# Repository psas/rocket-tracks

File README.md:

rocket-tracks
=============

CAD files for the Rocket Tracks project

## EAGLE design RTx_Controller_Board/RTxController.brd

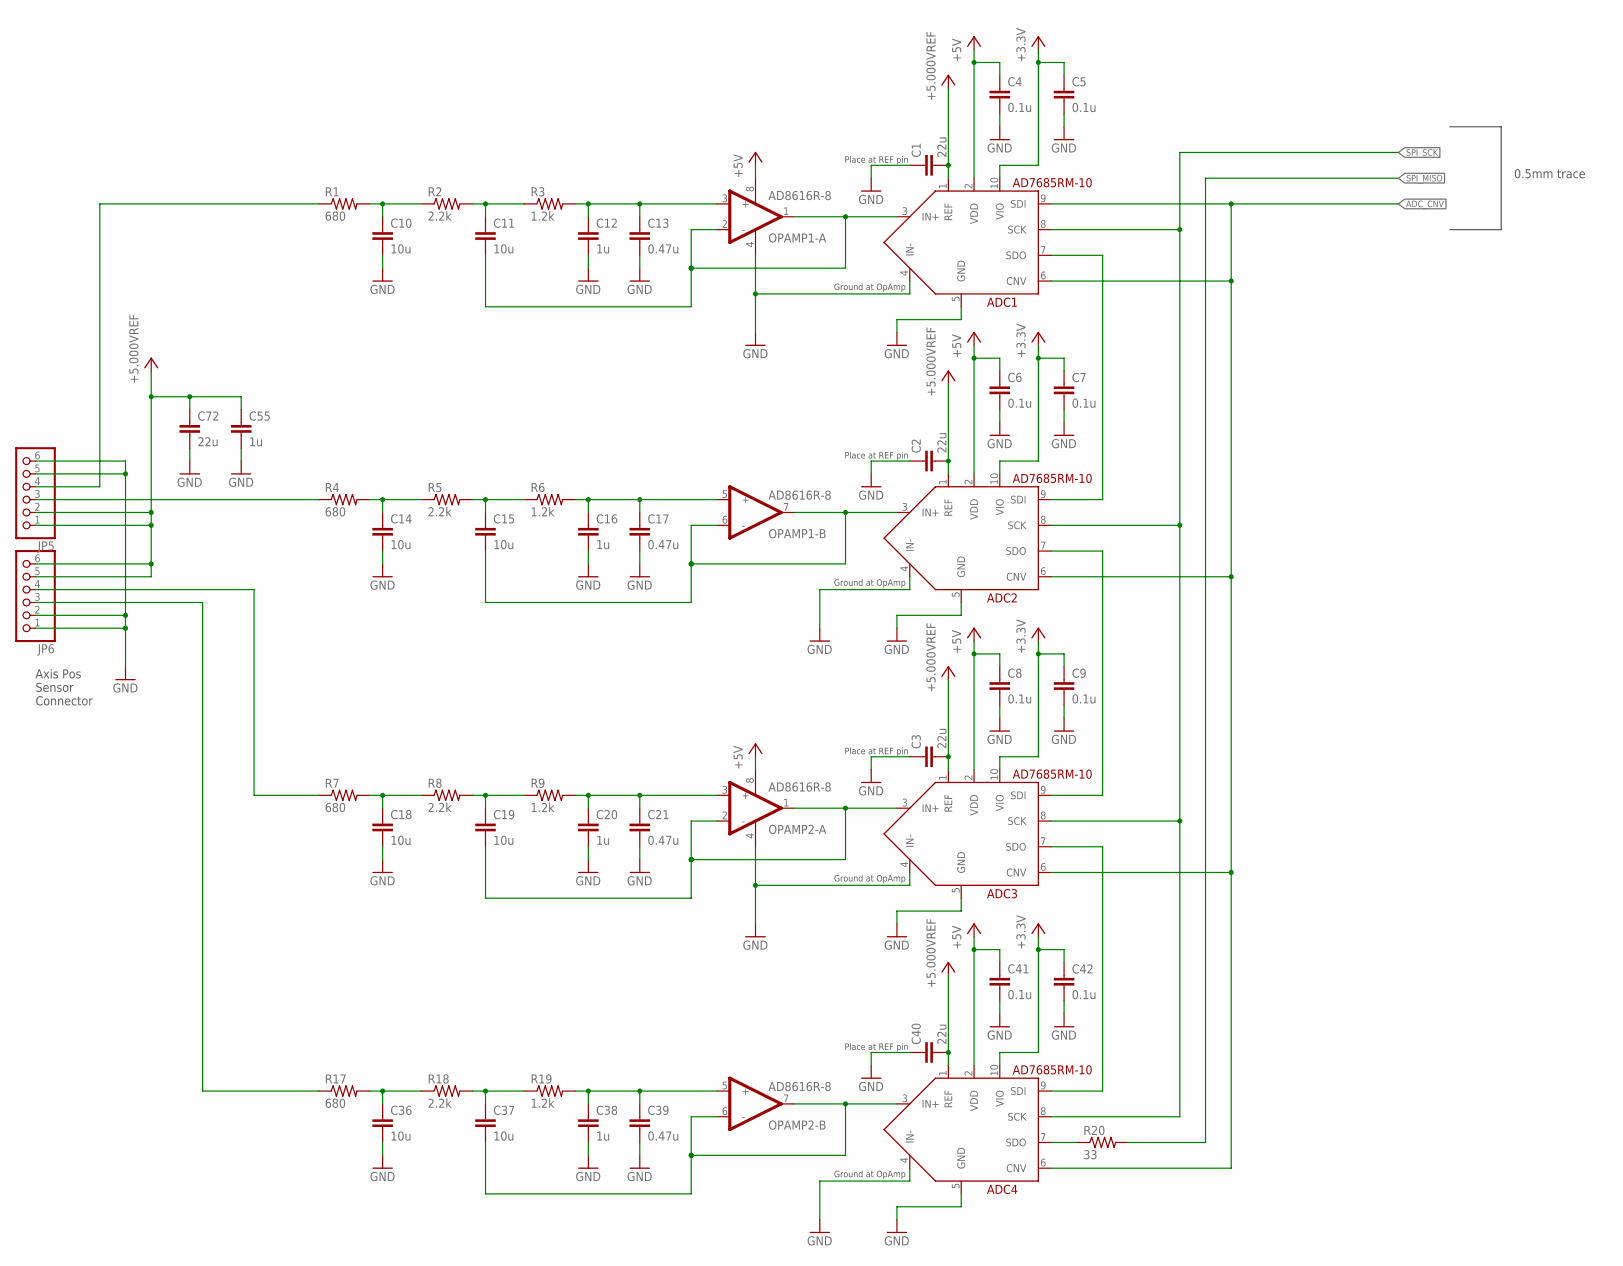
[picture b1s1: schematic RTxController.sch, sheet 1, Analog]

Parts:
ADC1, ADC2, ADC3, ADC4: AD7685RM-10; MSOP-10
C1, C2, C3, C40, C72: 22u; C1206
C4, C5, C6, C7, C8, C9, C41, C42: 0.1u; C0402
C10, C11, C14, C15, C18, C19, C36, C37: 10u; C1206
C12, C16, C20, C38, C55: 1u; C0805
C13, C17, C21, C39: 0.47u; C0805
JP5, JP6: PINHD-1X6; 1X06
OPAMP1, OPAMP2: AD8616R-8; SOIC8
R1, R4, R7, R17: 680; R0402
R2, R5, R8, R18: 2.2k; R0402
R3, R6, R9, R19: 1.2k; R0402
R20: 33; R0402

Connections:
+3.3V: ADC1.10 (VIO), ADC2.10 (VIO), ADC3.10 (VIO), ADC4.10 (VIO), C5.1, C7.1, C9.1, C42.1; also elsewhere on the board
+5.000VREF: ADC1.1 (REF), ADC2.1 (REF), ADC3.1 (REF), ADC4.1 (REF), C1.2, C2.2, C3.2, C40.2, C55.1, C72.1, JP5.1, JP5.2, JP6.5, JP6.6; also elsewhere on the board
+5V: ADC1.2 (VDD), ADC2.2 (VDD), ADC3.2 (VDD), ADC4.2 (VDD), C4.1, C6.1, C8.1, C41.1, OPAMP1.8 (V+), OPAMP2.8 (V+); also elsewhere on the board
ADC1_IN+: ADC1.3 (IN+), C11.2, OPAMP1.1 (OUT_A), OPAMP1.2 (-)
ADC2_IN+: ADC2.3 (IN+), C15.2, OPAMP1.6 (-), OPAMP1.7 (OUT_B)
ADC3_IN+: ADC3.3 (IN+), C19.2, OPAMP2.1 (OUT_A), OPAMP2.2 (-)
ADC4_IN: ADC4.3 (IN+), C37.2, OPAMP2.6 (-), OPAMP2.7 (OUT_B)
ADC_CNV: ADC1.6 (CNV), ADC1.9 (SDI), ADC2.6 (CNV), ADC3.6 (CNV), ADC4.6 (CNV); also elsewhere on the board
AXIS3_IN: JP6.4, R7.1
AXIS4_IN: JP6.3, R17.1
GND: ADC1.4 (IN-), ADC1.5 (GND), ADC2.4 (IN-), ADC2.5 (GND), ADC3.4 (IN-), ADC3.5 (GND), ADC4.4 (IN-), ADC4.5 (GND), C1.1, C2.1, C3.1, C4.2, C5.2, C6.2, C7.2, C8.2, C9.2, C10.2, C12.2, C13.2, C14.2, C16.2, C17.2, C18.2, C20.2, C21.2, C36.2, C38.2, C39.2, C40.1, C41.2, C42.2, C55.2, C72.2, JP5.5, JP5.6, JP6.1, JP6.2, OPAMP1.4 (V-), OPAMP2.4 (V-); also elsewhere on the board
LAT_AXIS_IN: JP5.4, R1.1
unnamed: C12.1, C13.1, OPAMP1.3 (+), R3.2
unnamed: C16.1, C17.1, OPAMP1.5 (+), R6.2
unnamed: C38.1, C39.1, OPAMP2.5 (+), R19.2
unnamed: C11.1, R2.2, R3.1
unnamed: C37.1, R18.2, R19.1
unnamed: C15.1, R5.2, R6.1
unnamed: C36.1, R17.2, R18.1
unnamed: C14.1, R4.2, R5.1
unnamed: C20.1, C21.1, OPAMP2.3 (+), R9.2
unnamed: C19.1, R8.2, R9.1
unnamed: C18.1, R7.2, R8.1
unnamed: C10.1, R1.2, R2.1
SDO1: ADC1.7 (SDO), ADC2.9 (SDI)
SDO2: ADC2.7 (SDO), ADC3.9 (SDI)
SDO3: ADC3.7 (SDO), ADC4.9 (SDI)
SDO4: ADC4.7 (SDO), R20.1
SPI_MISO: R20.2; also elsewhere on the board
SPI_SCK: ADC1.8 (SCK), ADC2.8 (SCK), ADC3.8 (SCK), ADC4.8 (SCK); also elsewhere on the board
VERT_AXIS_IN: JP5.3, R4.1

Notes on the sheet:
Axis Pos Sensor Connector
Ground at OpAmp
Place at REF pin
0.5mm trace

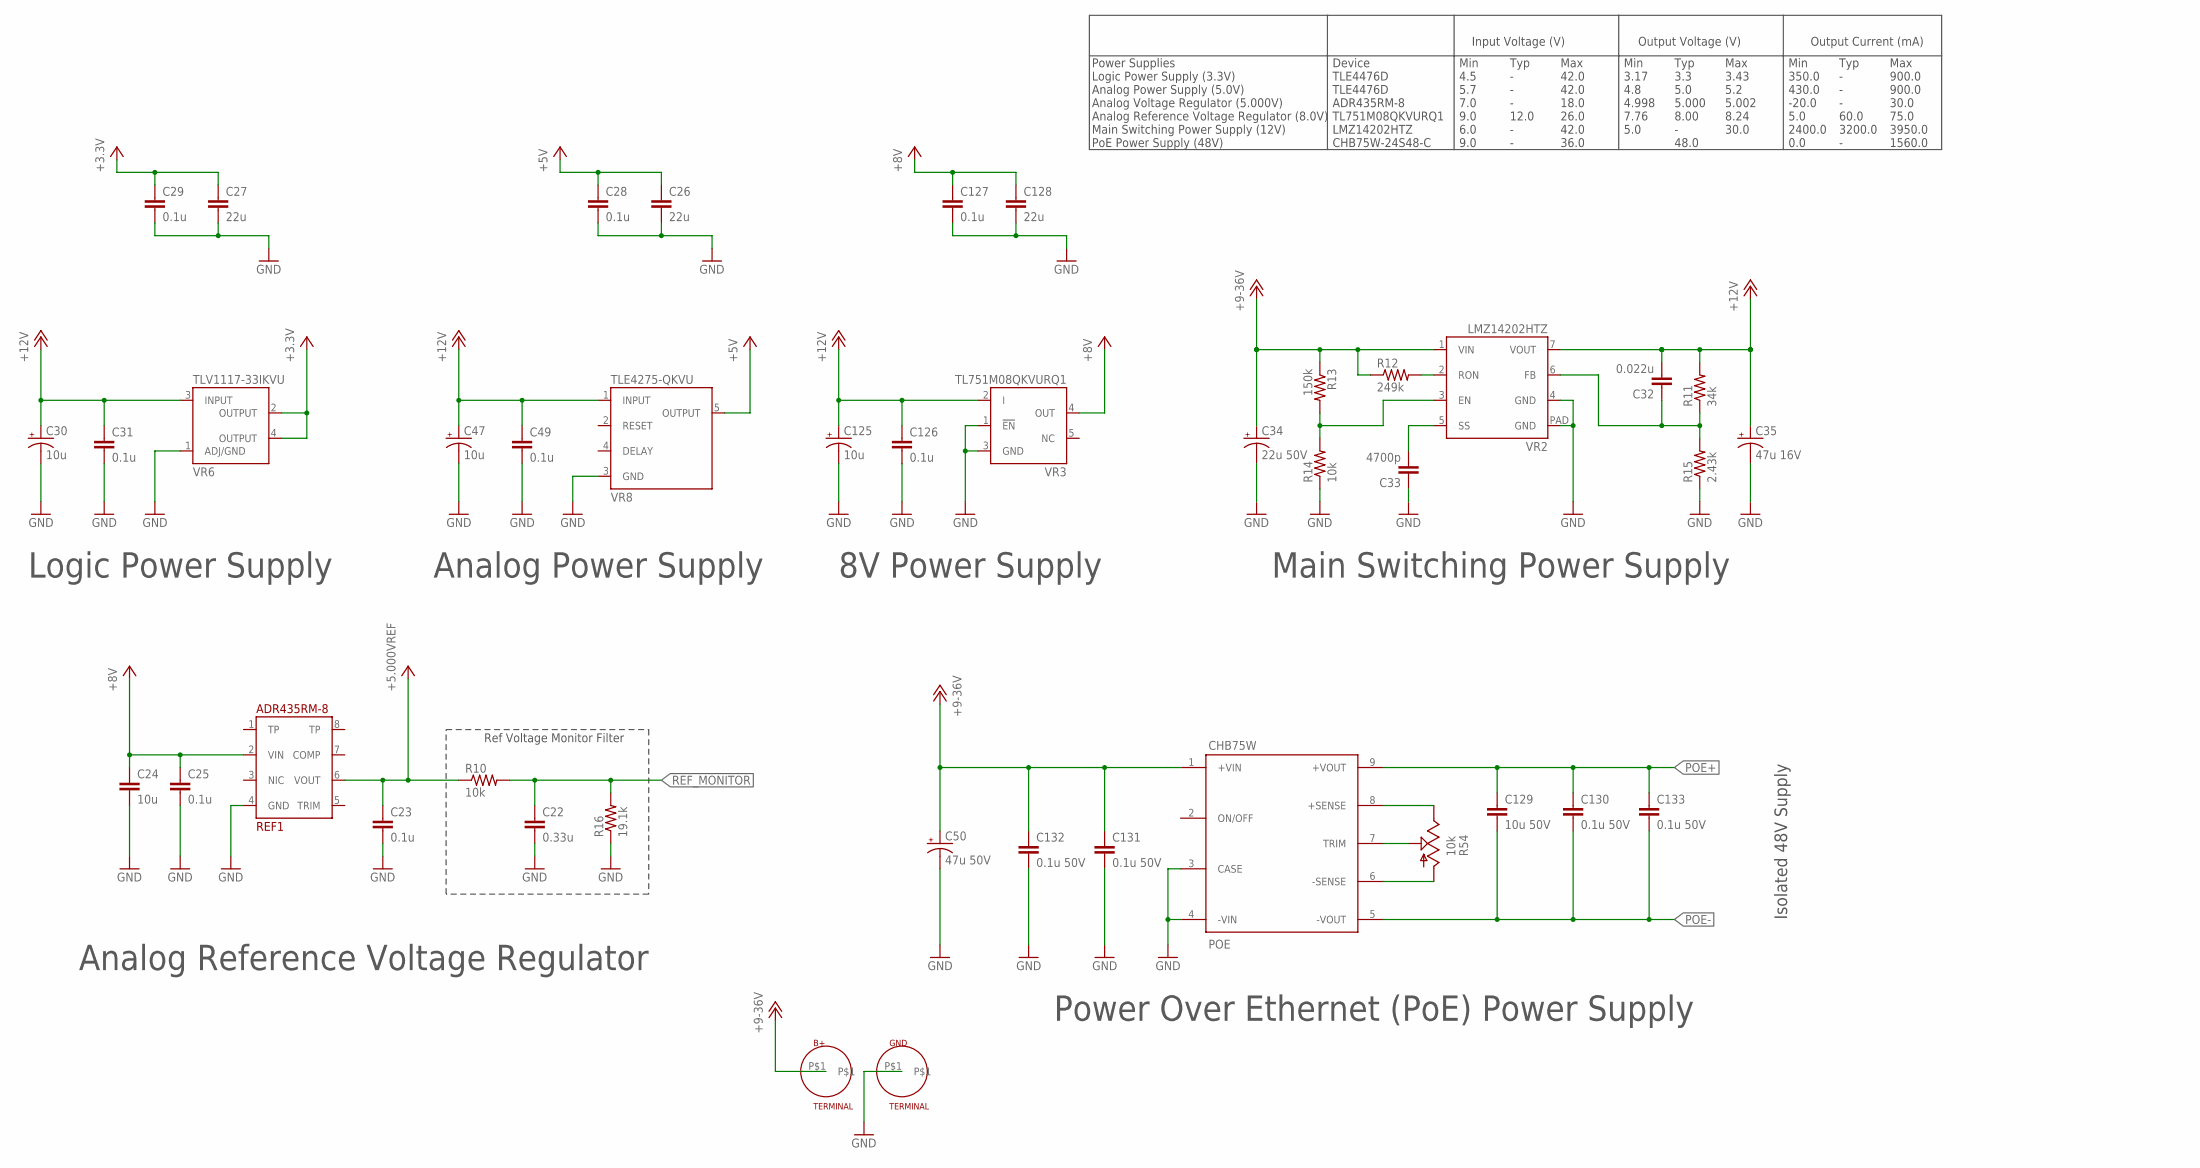
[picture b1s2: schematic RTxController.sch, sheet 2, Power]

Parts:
B+: TERMINAL; TERMINAL_RELAY
C22: 0.33u; C0603
C23, C25, C28, C29, C31, C49, C126, C127: 0.1u; C0402
C24: 10u; C1206
C26, C27, C128: 22u; C1206
C30, C47, C125: 10u; PANASONIC_B
C32: 0.022u; C0402
C33: 4700p; C0402
C34: 22u 50V; PANASONIC_B
C35: 47u 16V; PANASONIC_B
C50: 47u 50V; PANASONIC_C
C129: 10u 50V; C1206
C130, C131, C132, C133: 0.1u 50V; C0402
GND: TERMINAL; TERMINAL_RELAY
POE: CHB75W
R10: 10k; R0402
R11: 34k; R0603
R12: 249k; R0603
R13: 150k; R0603
R14: 10k; R0603
R15: 2.43k; R0603
R16: 19.1k; R0402
R54: 10k; 3223W
REF1: ADR435RM-8; SOIC8
VR2: LMZ14202HTZ; PFM-7
VR3: TL751M08QKVURQ1; PG-TO252-5-11
VR6: TLV1117-33IKVU; PG-TO252-3-11
VR8: TLE4275-QKVU; PG-TO252-5-11

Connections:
+3.3V: C27.1, C29.1, VR6.2 (OUTPUT), VR6.4 (OUTPUT); also elsewhere on the board
+5.000VREF: C23.1, R10.1, REF1.6 (VOUT); also elsewhere on the board
+5V: C26.1, C28.1, VR8.5 (OUTPUT); also elsewhere on the board
+8V: C24.1, C25.1, C127.1, C128.1, REF1.2 (VIN), VR3.4 (OUT)
+9-36V: B+.P$1, C34.+, C50.+, C131.1, C132.1, POE.1 (+VIN), R12.1, R13.1, VR2.1 (VIN)
+12V: C30.+, C31.1, C32.2, C35.+, C47.+, C49.1, C125.+, C126.1, R11.2, VR2.7 (VOUT), VR3.2 (I), VR6.3 (INPUT), VR8.1 (INPUT)
GND: C22.2, C23.2, C24.2, C25.2, C26.2, C27.2, C28.2, C29.2, C30.-, C31.2, C33.1, C34.-, C35.-, C47.-, C49.2, C50.-, C125.-, C126.2, C127.2, C128.2, C131.2, C132.2, GND.P$1, POE.3 (CASE), POE.4 (-VIN), R14.1, R15.1, R16.1, REF1.4 (GND), VR2.4 (GND), VR2.PAD (GND), VR3.1 (!EN!), VR3.3 (GND), VR6.1 (ADJ/GND), VR8.3 (GND); also elsewhere on the board
unnamed: R12.2, VR2.2 (RON)
unnamed: R13.2, R14.2, VR2.3 (EN)
unnamed: C33.2, VR2.5 (SS)
unnamed: C32.1, R11.1, R15.2, VR2.6 (FB)
unnamed: POE.7 (TRIM), R54.2 (S)
unnamed: POE.6 (-SENSE), R54.1 (A)
unnamed: POE.8 (+SENSE), R54.3 (E)
POE+: C129.1, C130.1, C133.1, POE.9 (+VOUT); also elsewhere on the board
POE-: C129.2, C130.2, C133.2, POE.5 (-VOUT); also elsewhere on the board
REF_MONITOR: C22.1, R10.2, R16.2; also elsewhere on the board

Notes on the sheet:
Logic Power Supply
Main Switching Power Supply
Analog Reference Voltage Regulator
Power Over Ethernet (PoE) Power Supply
Isolated 48V Supply
8V Power Supply
Ref Voltage Monitor Filter
Power Supplies Logic Power Supply (3.3V) Analog Power Supply (5.0V) Analog Voltage Regulator (5.000V) Analog Reference Voltage Regulator (8.0V) Main Switching Power Supply (12V) PoE Power Supply (48V)
Device TLE4476D TLE4476D ADR435RM-8 TL751M08QKVURQ1 LMZ14202HTZ CHB75W-24S48-C
Min 4.5 5.7 7.0 9.0 6.0 9.0
Typ - - - 12.0 - -
Max 42.0 42.0 18.0 26.0 42.0 36.0
Min 3.17 4.8 4.998 7.76 5.0
Typ 3.3 5.0 5.000 8.00 - 48.0
Max 3.43 5.2 5.002 8.24 30.0
Min 350.0 430.0 -20.0 5.0 2400.0 0.0
Typ - - - 60.0 3200.0 -
Max 900.0 900.0 30.0 75.0 3950.0 1560.0
Input Voltage (V) Output Voltage (V) Output Current (mA)
Analog Power Supply

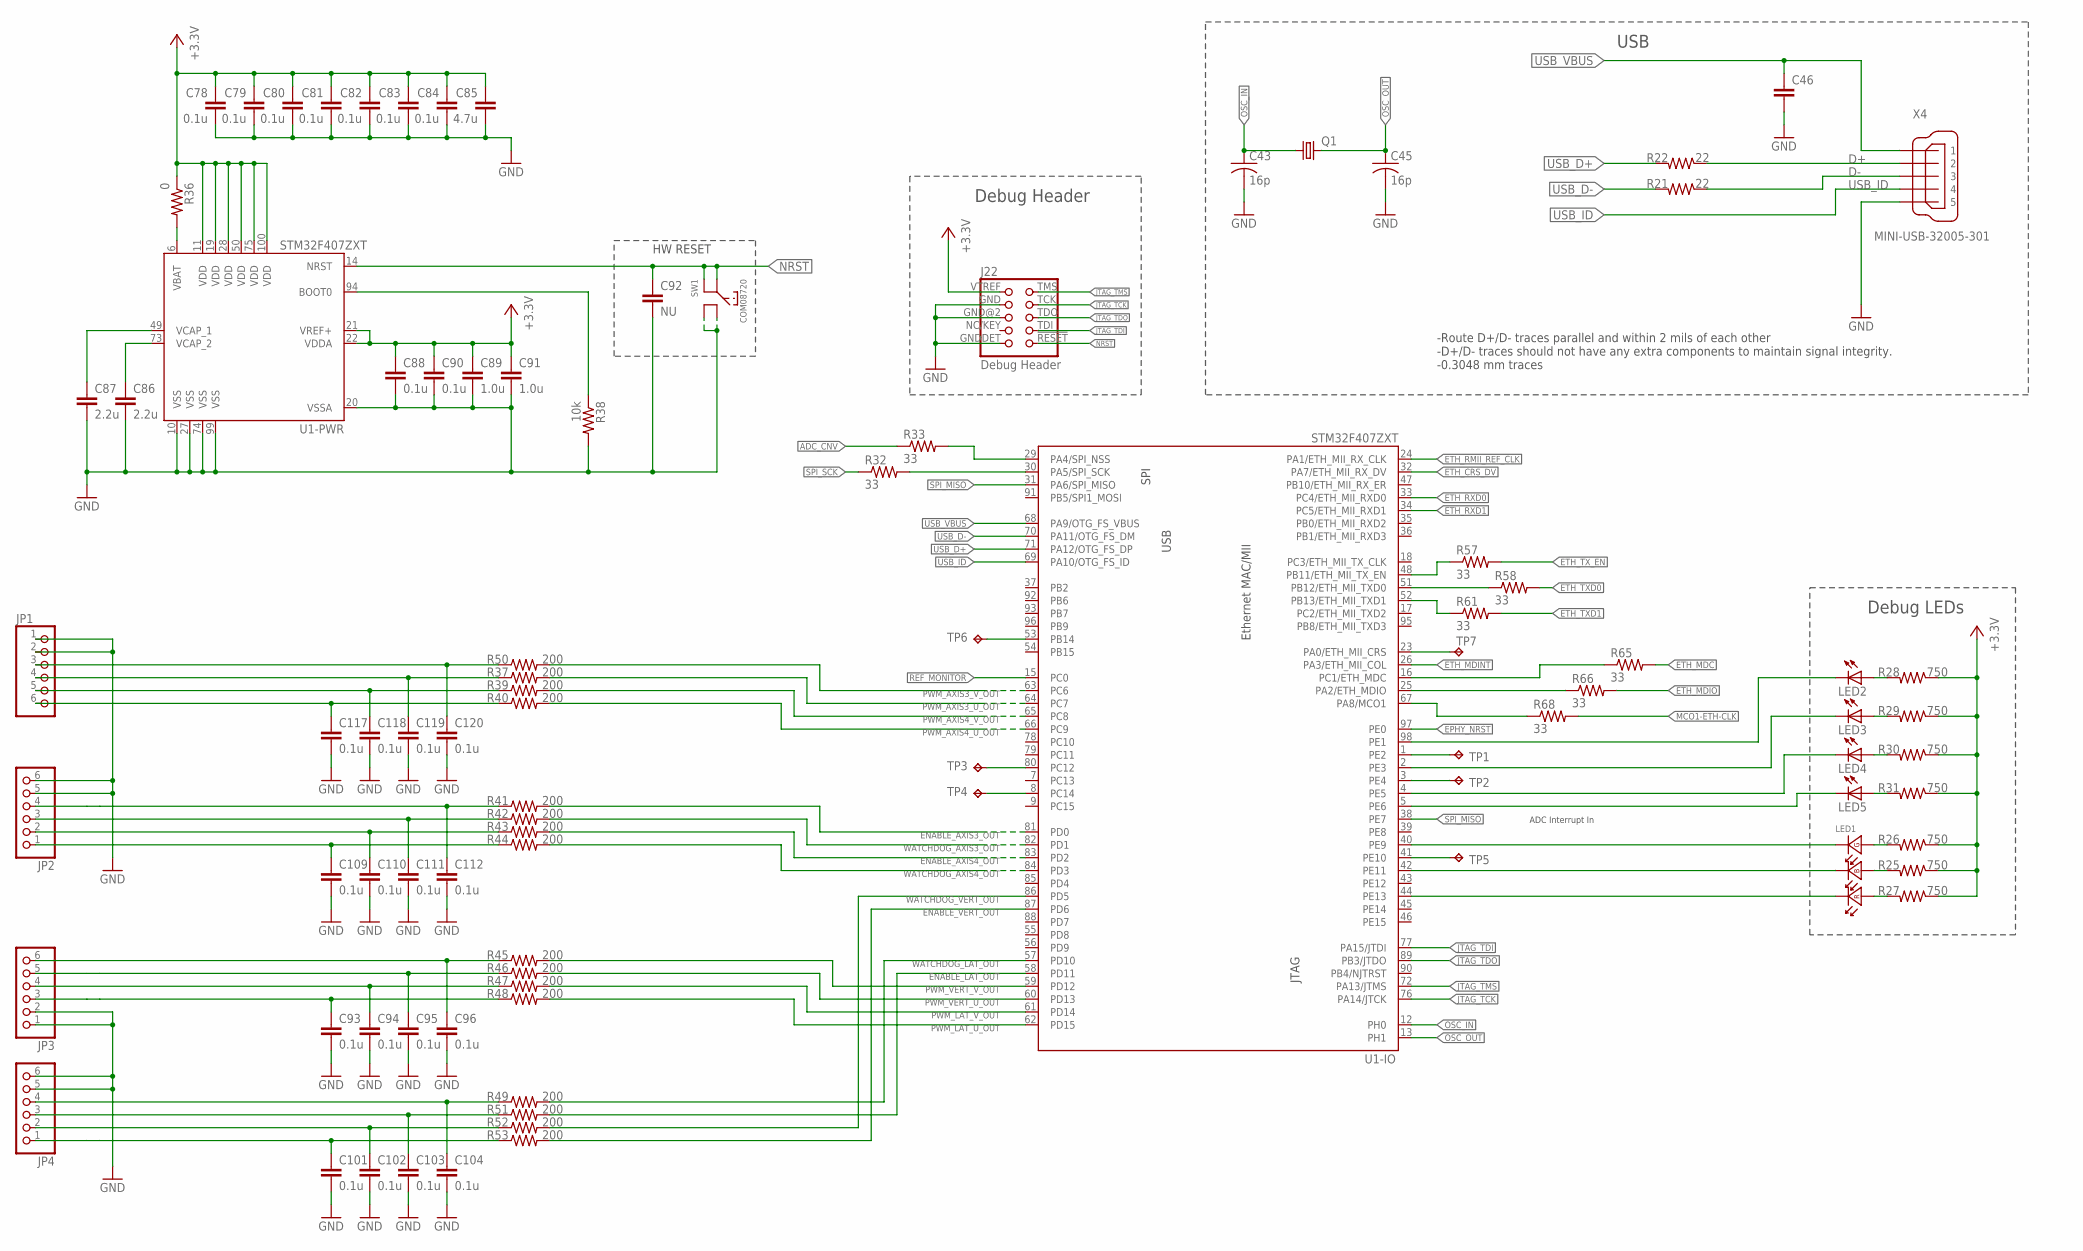
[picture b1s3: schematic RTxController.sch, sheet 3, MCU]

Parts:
C43, C45: 16p; C0402
C46: C-EUC0603; C0603
C78, C79, C80, C81, C82, C83, C84, C88, C90: 0.1u; C0402
C85: 4.7u; C0603
C86, C87: 2.2u; C0402
C89, C91: 1.0u; C0402
C92: NU; C0402
C93, C94, C95, C96, C101, C102, C103, C104, C109, C110, C111, C112, C117, C118, C119, C120: 0.1u; C0603
J22: Debug Header; 1.27MM_2X5
JP1, JP2, JP3, JP4: PINHD-1X6; 1X06
LED1: LED_RGB_PLCC-6; PLCC-6
LED2, LED3, LED4, LED5: LEDCHIP-LED0603; CHIP-LED0603
Q1: CRYSTALCTS406; CTS406
R21, R22: 22; R0402
R25, R26, R27, R28, R29, R30, R31: 750; R0402
R32, R33, R57, R58, R61, R65, R66, R68: 33; R0402
R36: 0; R0603
R37, R39, R40, R41, R42, R43, R44, R45, R46, R47, R48, R49, R50, R51, R52, R53: 200; R0603
R38: 10k; R0603
SW1: COM08720
TP1, TP2, TP3, TP4, TP5, TP6, TP7: TPTP06R; TP06R
U1: STM32F407ZXT; LQFP-100
X4: MINI-USB-32005-301; 32005-301

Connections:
+3.3V: C78.1, C79.1, C80.1, C81.1, C82.1, C83.1, C84.1, C85.1, C88.1, C89.1, C90.1, C91.1, J22.VTREF, R25.1, R26.1, R27.1, R28.1, R29.1, R30.1, R31.1, R36.1, U1.11 (VDD), U1.19 (VDD), U1.21 (VREF+), U1.22 (VDDA), U1.28 (VDD), U1.50 (VDD), U1.75 (VDD), U1.100 (VDD); also elsewhere on the board
ADC_CNV: R33.1; also elsewhere on the board
BOOT0: R38.1, U1.94 (BOOT0)
D+: R22.1, X4.2
D-: R21.1, X4.3
ENABLE_AXIS3_OUT: R41.2, U1.81 (PD0)
ENABLE_AXIS4_OUT: R43.2, U1.83 (PD2)
ENABLE_LAT_OUT: R51.2, U1.58 (PD11)
ENABLE_VERT_OUT: R53.2, U1.87 (PD6)
EPHY_NRST: U1.97 (PE0); also elsewhere on the board
ETH_CRS_DV: U1.32 (PA7/ETH_MII_RX_DV); also elsewhere on the board
ETH_MDC: R65.2; also elsewhere on the board
ETH_MDINT: U1.26 (PA3/ETH_MII_COL); also elsewhere on the board
ETH_MDIO: R66.2; also elsewhere on the board
ETH_RMII_REF_CLK: U1.24 (PA1/ETH_MII_RX_CLK); also elsewhere on the board
ETH_RXD0: U1.33 (PC4/ETH_MII_RXD0); also elsewhere on the board
ETH_RXD1: U1.34 (PC5/ETH_MII_RXD1); also elsewhere on the board
ETH_TXD0: R58.2; also elsewhere on the board
ETH_TXD1: R61.2; also elsewhere on the board
ETH_TX_EN: R57.2; also elsewhere on the board
GND: C43.2, C45.2, C46.2, C78.2, C79.2, C80.2, C81.2, C82.2, C83.2, C84.2, C85.2, C86.2, C87.2, C88.2, C89.2, C90.2, C91.2, C92.2, C93.2, C94.2, C95.2, C96.2, C101.2, C102.2, C103.2, C104.2, C109.2, C110.2, C111.2, C112.2, C117.2, C118.2, C119.2, C120.2, J22.GND, J22.GND@2 (GND), J22.GNDDET, JP1.1, JP1.2, JP2.5, JP2.6, JP3.1, JP3.2, JP4.5, JP4.6, R38.2, SW1.2, SW1.4, U1.10 (VSS), U1.20 (VSSA), U1.27 (VSS), U1.74 (VSS), U1.99 (VSS), X4.5; also elsewhere on the board
JTAG_TCK: J22.TCK, U1.76 (PA14/JTCK)
JTAG_TDI: J22.TDI, U1.77 (PA15/JTDI)
JTAG_TDO: J22.TDO, U1.89 (PB3/JTDO)
JTAG_TMS: J22.TMS, U1.72 (PA13/JTMS)
MCO1-ETH-CLK: R68.2; also elsewhere on the board
unnamed: LED2.A, R28.2
unnamed: LED3.A, R29.2
unnamed: LED1.3 (A), R26.2
unnamed: LED1.4 (A), R25.2
unnamed: LED1.1 (A), R27.2
unnamed: C96.1, JP3.6, R45.1
unnamed: R36.2, U1.6 (VBAT)
unnamed: C95.1, JP3.5, R46.1
unnamed: C94.1, JP3.4, R47.1
unnamed: C93.1, JP3.3, R48.1
unnamed: C104.1, JP4.4, R49.1
unnamed: C103.1, JP4.3, R51.1
unnamed: C102.1, JP4.2, R52.1
unnamed: C101.1, JP4.1, R53.1
unnamed: C112.1, JP2.4, R41.1
unnamed: C111.1, JP2.3, R42.1
unnamed: C110.1, JP2.2, R43.1
unnamed: C109.1, JP2.1, R44.1
unnamed: LED4.A, R30.2
unnamed: LED5.A, R31.2
unnamed: LED1.5 (K), U1.42 (PE11)
unnamed: LED1.2 (K), U1.40 (PE9)
unnamed: LED1.6 (K), U1.44 (PE13)
unnamed: C120.1, JP1.3, R50.1
unnamed: C119.1, JP1.4, R37.1
unnamed: C118.1, JP1.5, R39.1
unnamed: C117.1, JP1.6, R40.1
unnamed: LED5.C, U1.5 (PE6)
unnamed: LED4.C, U1.4 (PE5)
unnamed: LED3.C, U1.2 (PE3)
unnamed: LED2.C, U1.98 (PE1)
unnamed: R33.2, U1.29 (PA4/SPI_NSS)
unnamed: R57.1, U1.48 (PB11/ETH_MII_TX_EN)
unnamed: R61.1, U1.52 (PB13/ETH_MII_TXD1)
unnamed: R58.1, U1.51 (PB12/ETH_MII_TXD0)
unnamed: R65.1, U1.16 (PC1/ETH_MDC)
unnamed: R66.1, U1.25 (PA2/ETH_MDIO)
unnamed: R68.1, U1.67 (PA8/MCO1)
NRST: C92.1, J22.!RESET, SW1.1, SW1.3, U1.14 (NRST)
OSC_IN: C43.1, Q1.1, U1.12 (PH0)
OSC_OUT: C45.1, Q1.3 (2), U1.13 (PH1)
PWM_AXIS3_U_OUT: R37.2, U1.64 (PC7)
PWM_AXIS3_V_OUT: R50.2, U1.63 (PC6)
PWM_AXIS4_U_OUT: R40.2, U1.66 (PC9)
PWM_AXIS4_V_OUT: R39.2, U1.65 (PC8)
PWM_LAT_U_OUT: R48.2, U1.62 (PD15)
PWM_LAT_V_OUT: R47.2, U1.61 (PD14)
PWM_VERT_U_OUT: R46.2, U1.60 (PD13)
PWM_VERT_V_OUT: R45.2, U1.59 (PD12)
REF_MONITOR: U1.15 (PC0); also elsewhere on the board
SPI_MISO: U1.31 (PA6/SPI_MISO), U1.38 (PE7); also elsewhere on the board
SPI_SCK: R32.1; also elsewhere on the board
SPI_SCK_MCU: R32.2, U1.30 (PA5/SPI_SCK)
TP1: TP1.TP, U1.1 (PE2)
TP2: TP2.TP, U1.3 (PE4)
TP3: TP3.TP, U1.80 (PC12)
TP4: TP4.TP, U1.8 (PC14)
TP5: TP5.TP, U1.41 (PE10)
TP6: TP6.TP, U1.53 (PB14)
TP7: TP7.TP, U1.23 (PA0/ETH_MII_CRS)
USB_D+: R22.2, U1.71 (PA12/OTG_FS_DP)
USB_D-: R21.2, U1.70 (PA11/OTG_FS_DM)
USB_ID: U1.69 (PA10/OTG_FS_ID), X4.4
USB_VBUS: C46.1, U1.68 (PA9/OTG_FS_VBUS), X4.1
VCAP_1: C87.1, U1.49 (VCAP_1)
VCAP_2: C86.1, U1.73 (VCAP_2)
WATCHDOG_AXIS3_OUT: R42.2, U1.82 (PD1)
WATCHDOG_AXIS4_OUT: R44.2, U1.84 (PD3)
WATCHDOG_LAT_OUT: R49.2, U1.57 (PD10)
WATCHDOG_VERT_OUT: R52.2, U1.86 (PD5)

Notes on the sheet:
HW RESET
ADC Interrupt In
Debug Header
USB
Debug LEDs
-Route D+/D- traces parallel and within 2 mils of each other -D+/D- traces should not have any extra components to maintain signal integrity. -0.3048 mm traces

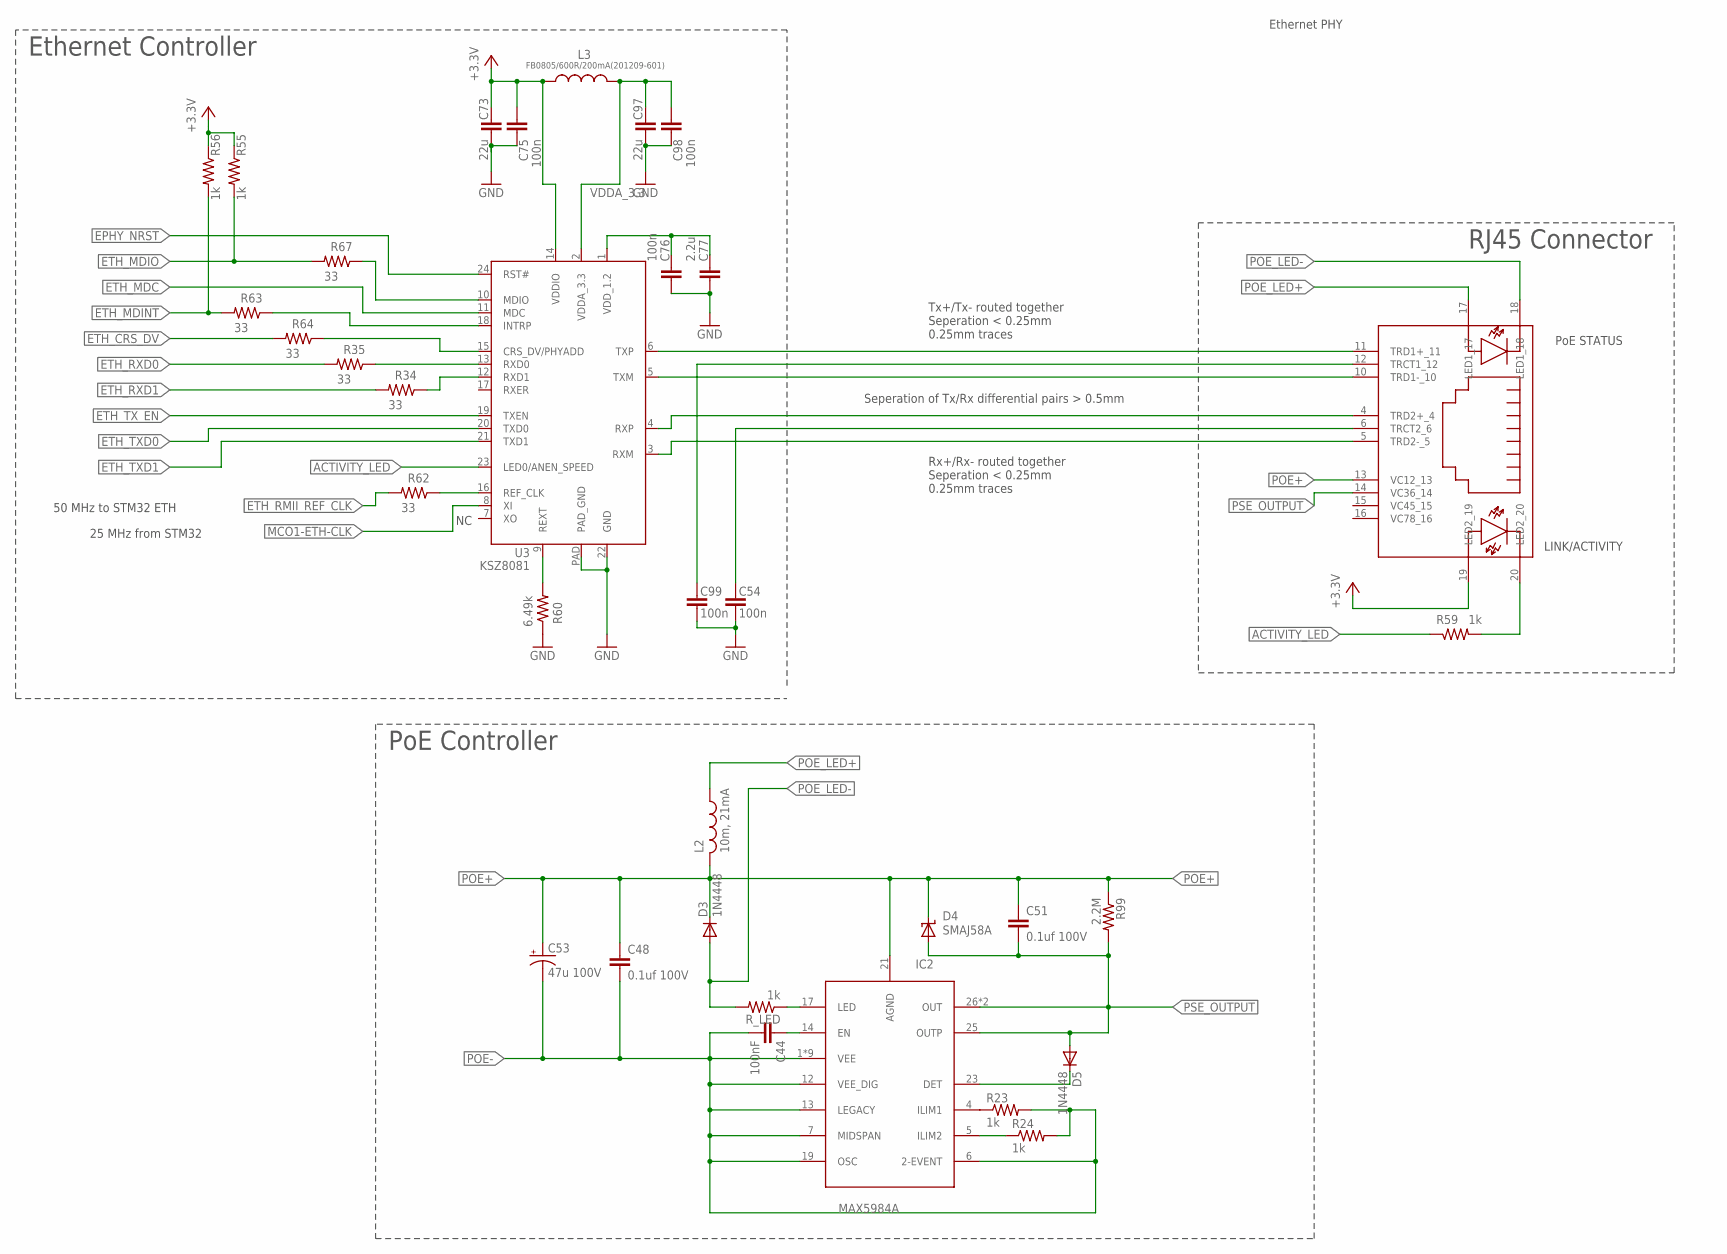
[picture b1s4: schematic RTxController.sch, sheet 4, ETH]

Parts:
C44: 100nF; C0805K
C48, C51: 0.1uf 100V; C0805K
C53: 47u 100V; PANASONIC_C
C54, C75, C76, C98, C99: 100n; 0402-C-NOSILK
C73, C97: 22u; 1206-C
C77: 2.2u; 0402-C-NOSILK
D3, D5: 1N4448; SOD-123
D4: SMAJ58A; SMBJ
IC2: MAX5984A; TQFN-28
L2: 10m, 21mA; 0204V
L3: FB0805/600R/200mA(201209-601); 0805-C-NOSILK
R23, R24: 1k; R0603
R34, R35, R62, R63, R64, R67: 33; 0402-C-NOSILK
R55, R56, R59: 1k; 0402-C-NOSILK
R60: 6.49k; 0402-C-NOSILK
R99: 2.2M; R0603
R_LED: 1k; R0603
U3: KSZ8081; QFN-24
X8: 0826-1X1T-GJ-F; MAGJACK-RJ45

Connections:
+3.3V: C73.2, C75.2, L3.2, R55.1, R56.1, U3.14 (VDDIO), X8.19 (LED2_19); also elsewhere on the board
ACTIVITY_LED: R59.1, U3.23 (LED0/ANEN_SPEED)
EPHY_NRST: U3.24 (RST#); also elsewhere on the board
ETH_CRS_DV: R64.2; also elsewhere on the board
ETH_MDC: U3.11 (MDC); also elsewhere on the board
ETH_MDINT: R56.2, R63.2; also elsewhere on the board
ETH_MDIO: R55.2, R67.2; also elsewhere on the board
ETH_RMII_REF_CLK: R62.2; also elsewhere on the board
ETH_RXD0: R35.2; also elsewhere on the board
ETH_RXD1: R34.2; also elsewhere on the board
ETH_TXD0: U3.20 (TXD0); also elsewhere on the board
ETH_TXD1: U3.21 (TXD1); also elsewhere on the board
ETH_TX_EN: U3.19 (TXEN); also elsewhere on the board
GND: C54.1, C73.1, C75.1, C76.2, C77.2, C97.1, C98.1, C99.1, R60.1, U3.22 (GND), U3.PAD (PAD_GND); also elsewhere on the board
MCO1-ETH-CLK: U3.8 (XI); also elsewhere on the board
unnamed: R59.2, X8.20 (LED2_20)
unnamed: U3.6 (TXP), X8.11 (TRD1+_11)
unnamed: U3.5 (TXM), X8.10 (TRD1-_10)
unnamed: U3.4 (RXP), X8.4 (TRD2+_4)
unnamed: U3.3 (RXM), X8.5 (TRD2-_5)
unnamed: IC2.17 (LED), R_LED.1
unnamed: C44.1, IC2.14 (EN)
unnamed: D5.P$2 (C), IC2.23 (DET)
unnamed: IC2.4 (ILIM1), R23.1
unnamed: IC2.5 (ILIM2), R24.1
unnamed: R35.1, U3.13 (RXD0)
unnamed: R34.1, U3.12 (RXD1)
unnamed: R62.1, U3.16 (REF_CLK)
unnamed: R60.2, U3.9 (REXT)
unnamed: C76.1, C77.1, U3.1 (VDD_1.2)
unnamed: C99.2, X8.12 (TRCT1_12)
unnamed: R63.1, U3.18 (INTRP)
unnamed: R64.1, U3.15 (CRS_DV/PHYADD)
unnamed: R67.1, U3.10 (MDIO)
POE+: C48.1, C51.1, C53.+, D3.P$2 (C), D4.C, IC2.21 (AGND), L2.2, R99.1, X8.13 (VC12_13); also elsewhere on the board
POE-: C44.2, C48.2, C53.-, IC2.1 (VEE), IC2.2 (VEE), IC2.3 (VEE), IC2.6 (2-EVENT), IC2.7 (MIDSPAN), IC2.8 (VEE), IC2.9 (VEE), IC2.10 (VEE), IC2.11 (VEE), IC2.12 (VEE_DIG), IC2.13 (LEGACY), IC2.15 (VEE), IC2.19 (OSC), IC2.PAD (VEE), R23.2, R24.2; also elsewhere on the board
POE_LED+: L2.1, X8.17 (LED1_17)
POE_LED-: D3.P$1 (A), R_LED.2, X8.18 (LED1_18)
PSE_OUTPUT: C51.2, D4.A, D5.P$1 (A), IC2.25 (OUTP), IC2.26 (OUT), IC2.27 (OUT), R99.2, X8.14 (VC36_14)
VDDA: C54.2, X8.6 (TRCT2_6)
VDDA_3.3: C97.2, C98.2, L3.1, U3.2 (VDDA_3.3)

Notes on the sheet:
Ethernet PHY
LINK/ACTIVITY
25 MHz from STM32
50 MHz to STM32 ETH
PoE STATUS
PoE Controller
Ethernet Controller
RJ45 Connector
Tx+/Tx- routed together Seperation < 0.25mm 0.25mm traces
Rx+/Rx- routed together Seperation < 0.25mm 0.25mm traces
Seperation of Tx/Rx differential pairs > 0.5mm

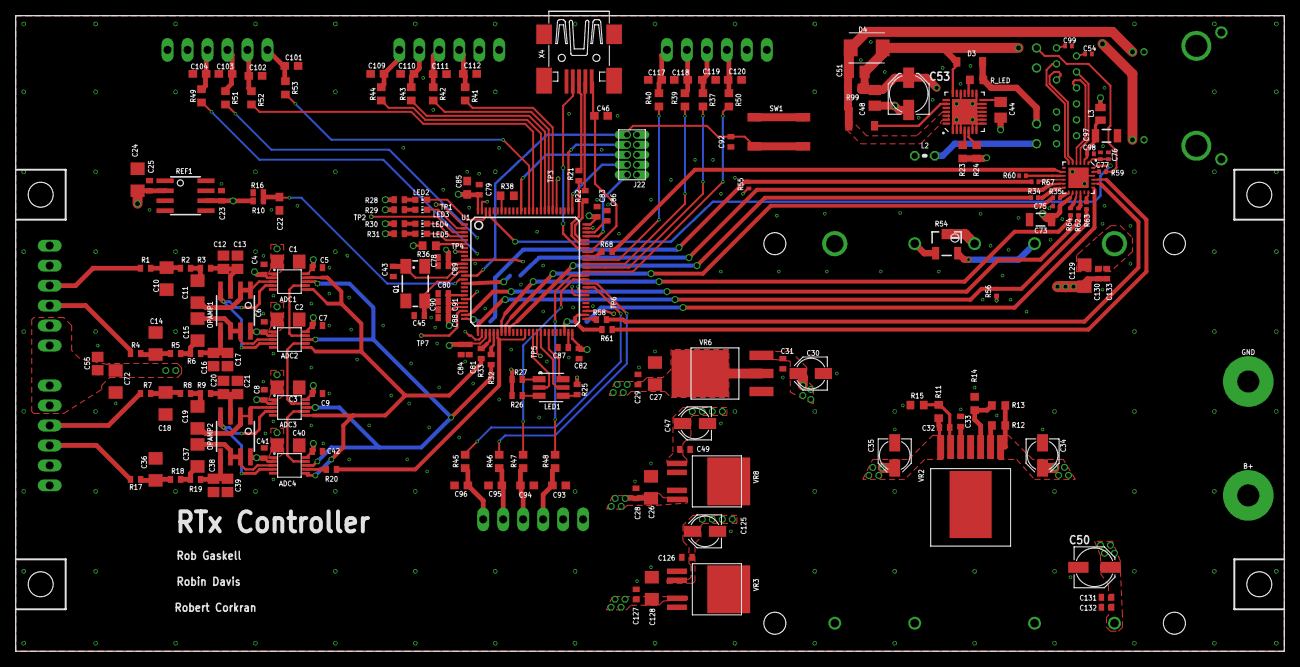
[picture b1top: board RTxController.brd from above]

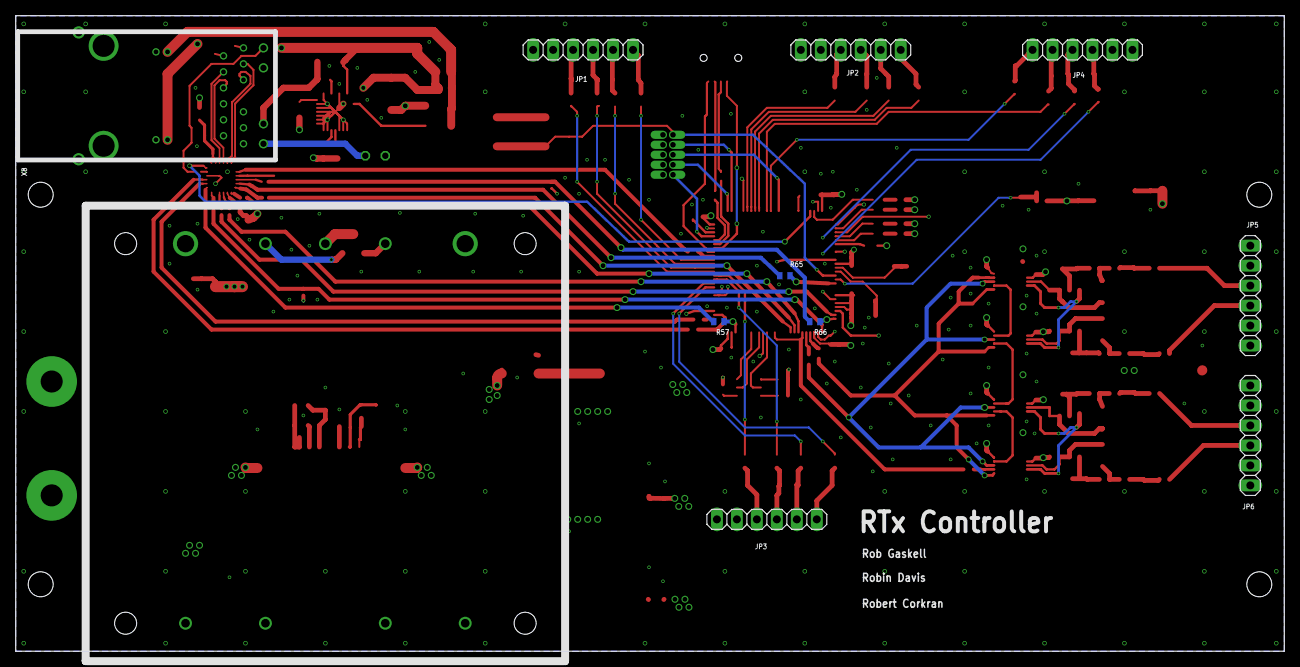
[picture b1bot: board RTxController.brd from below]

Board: 4 copper layers, 161.3 x 80.8 mm, 217 parts (11 on the bottom side), 159 nets.

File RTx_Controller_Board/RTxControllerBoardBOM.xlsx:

RTx ID | Order Qty | Order PN | Notes | Value | Device | Package | Qty | Parts | Description | MF | MPN | OC_FARNELL | OC_NEWARK | TP_SIGNAL_NAME | VARIANT
 | 3 |  | Andrew |  | CRYSTALCTS406 | CTS406 | 1 | Q1 | CRYSTAL |  |  | unknown | unknown
 | 12 | 160-1445-1-ND |  |  | LEDCHIP-LED0603 | CHIP-LED0603 | 4 | LED2, LED3, LED4, LED5 | LED
 | 3 |  | Andrew |  | LED_RGB_PLCC-6 | PLCC-6 | 1 | LED1 | RGB LED with separate contacts for all 3 chips
 | 18 | S9414-ND | SWR25X |  | PINHD-1X6 | 1X06 | 6 | JP1, JP2, JP3, JP4, JP5, JP6 | PIN HEADER
 | 12 | S9436-ND | SWH25X |  | Female-1X6 Polarized |  | 6
 | 180 | S9473CT-ND |  |  | Connector Terminals |  | 53
 | 10 | P0.0GCT-ND |  | 0 | R-US_R0603 | R0603 | 1 | R36 | RESISTOR, American symbol
 | 10 | 587-1224-1-ND |  | 0.022u | C-EUC0402 | C0402 | 1 | C32 | CAPACITOR, European symbol
 | 80 | 587-1227-1-ND |  | 0.1u | C-EUC0402 | C0402 | 25 | C4, C5, C6, C7, C8, C9, C23, C25, C28, C29, C31, C41, C42, C49, C78, C79, C80, 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 | CAPACITOR, European symbol
 | 50 | 399-1096-1-ND |  | 0.1u | C-EUC0603 | C0603 | 16 | C93, C94, C95, C96, C101, C102, C103, C104, C109, C110, C111, C112, C117, C118,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 | CAPACITOR, European symbol
 | 12 | 445-5942-1-ND |  | 0.1u 50V | C-EUC0402 | C0402 | 4 | C131, C132, C130, C133 | CAPACITOR, European symbol
 | 10 | 399-3486-1-ND |  | 0.1uf 100V | C-EUC0805K | C0805K | 2 | C48, C51 | CAPACITOR, European symbol
 | 10 | 445-5126-1-ND |  | 0.33u | C-EUC0603 | C0603 | 1 | C22 | CAPACITOR, European symbol
 | 15 | 587-1282-1-ND |  | 0.47u | C-EUC0805 | C0805 | 4 | C13, C17, C21, C39 | CAPACITOR, European symbol
 | 10 | 507-1569-ND | Robert | 0826-1X1T-GJ-F | 0826-1X1T-GJ-F | MAGJACK-RJ45 | 1 | X8
 | 25 | 587-1231-1-ND |  | 1.0u | C-EUC0402 | C0402 | 7 | C89, C91, C54, C75, C76, C98, C99 | CAPACITOR, European symbol
 | 15 | P1.20KLCT-ND |  | 1.2k | R-US_R0402 | R0402 | 4 | R3, R6, R9, R19 | RESISTOR, American symbol
 | 10 | 311-1142-1-ND |  | 100nF | C-EUC0805K | C0805K | 1 | C44 | CAPACITOR, European symbol
 | 10 | p10.0KLCT-ND |  | 10k | R-US_R0402 | R0402 | 1 | R10 | RESISTOR, American symbol
 | 10 | P10.0KHCT-ND |  | 10k | R-US_R0603 | R0603 | 2 | R14, R38 | RESISTOR, American symbol
 | 10 | 3223W-1-103-ND | Robert | 10k | TRIM_US-3223W | 3223W | 1 | R54 | POTENTIOMETER
 | 10 | AIAP-01-103-K-TCT-ND | Robert | 10m, 21mA | L-US0204V | 0204V | 1 | L2 | INDUCTOR, American symbol
 | 30 | 1276-1804-1-ND |  | 10u | C-EUC1206 | C1206 | 9 | C10, C11, C14, C15, C18, C19, C24, C36, C37 | CAPACITOR, European symbol
 | 10 | 1276-1119-1-ND | 0603 | 10u | C-USC0402 | C0402 | 1 | C46 | CAPACITOR, American symbol
 | 10 | PCE3895TR-ND |  | 10u | CPOL-USB | PANASONIC_B | 3 | C30, C47, C125 | POLARIZED CAPACITOR, American symbol
 | 10 | P150KHCT-ND |  | 150k | R-US_R0603 | R0603 | 1 | R13 | RESISTOR, American symbol
 | 10 | 399-11118-1-ND |  | 16p | C-USC0402 | C0402 | 2 | C43, C45 | CAPACITOR, American symbol
 | 10 | P19.1KLCT-ND |  | 19.1k | R-US_R0402 | R0402 | 1 | R16 | RESISTOR, American symbol
 | 10 | 1N4448W-FDICT-ND |  | 1N4448 | 1N4448 | SOD-123 | 2 | D3, D5
 | 15 | P1.00KLCT-ND |  | 1k | R-US_0402-C-NOSILK | 0402-C-NOSILK | 3 | R55, R56, R59 | RESISTOR, American symbol
 | 15 | P1.00KHCT-ND |  | 1k | R-US_R0603 | R0603 | 3 | R23, R24, R_LED | RESISTOR, American symbol
 | 20 | 399-1284-1-ND |  | 1u | C-EUC0805 | C0805 | 5 | C12, C16, C20, C38, C55 | CAPACITOR, European symbol
 | 10 | P2.20MHCT-ND |  | 2.2M | R-US_R0603 | R0603 | 1 | R99 | RESISTOR, American symbol
 | 15 | P2.20KLCT-ND |  | 2.2k | R-US_R0402 | R0402 | 4 | R2, R5, R8, R18 | RESISTOR, American symbol
 | 15 | 445-6847-1-ND |  | 2.2u | C-EU0402-C-NOSILK | 0402-C-NOSILK | 3 | C77, C86, C87 | CAPACITOR, European symbol
 | 10 | P2.43KHCT-ND |  | 2.43k | R-US_R0603 | R0603 | 1 | R15 | RESISTOR, American symbol
 | 55 | P200-HCT-ND |  | 200 | R-US_R0603 | R0603 | 16 | R37, R39, R40, R41, R42, R43, R44, R45, R46, R47, R48, R49, R50, R51, R52, R53 | RESISTOR, American symbol
 | 10 | P22.0LCT-ND |  | 22 | R-US_R0402 | R0402 | 2 | R21, R22 | RESISTOR, American symbol
 | 35 | 1276-3047-1-ND |  | 22u | C-EUC1206 | C1206 | 10 | C1, C2, C3, C26, C27, C40, C72, C128, C73, C97 | CAPACITOR, European symbol
 | 5 | PCE3920TR-ND |  | 22u 50V | CPOL-USB | PANASONIC_B | 1 | C34 | POLARIZED CAPACITOR, American symbol
 | 5 | 445-5998-1-ND |  | 10u 50V | C-EUC1206 | C1206 | 1 | C129 | CAPACITOR, European symbol
 | 5 | P249KHCT-ND |  | 249k | R-US_R0603 | R0603 | 1 | R12 | RESISTOR, American symbol
 | 55 | P33.0LCT-ND |  | 33 | R-US_R0402 | R0402 | 15 | R20, R32, R33, R34, R35, R57, R58, R61, R62, R63, R64, R65, R66, R67, R68 | RESISTOR, American symbol
 | 10 | P34.0KHCT-ND |  | 34k | R-US_R0603 | R0603 | 1 | R11 | RESISTOR, American symbol
 | 10 | 587-1441-1-ND |  | 4.7u | C-EUC0603 | C0603 | 1 | C85 | CAPACITOR, European symbol
 | 10 | 1276-1571-1-ND |  | 4700p | C-EUC0402 | C0402 | 1 | C33 | CAPACITOR, European symbol
 | 10 | PCE3890CT-ND |  | 47u 16V | CPOL-USB | PANASONIC_B | 1 | C35 | POLARIZED CAPACITOR, American symbol
 | 10 | PCE3929CT-ND |  | 47u 50V | CPOL-USB | PANASONIC_B | 1 | C135 | POLARIZED CAPACITOR, American symbol
 | 10 | PCE3497CT-ND |  | 47uf 100V | CPOL-USB | PANASONIC_B | 1 | C52 | CAPACITOR, European symbol
 | 10 | P6.49KLCT-ND |  | 6.49k | R-US_0402-C-NOSILK | 0402-C-NOSILK | 1 | R60 | RESISTOR, American symbol
 | 15 | P680LCT-ND |  | 680 | R-US_R0402 | R0402 | 4 | R1, R4, R7, R17 | RESISTOR, American symbol
 | 25 | P750LCT-ND |  | 750 | R-US_R0402 | R0402 | 7 | R25, R26, R27, R28, R29, R30, R31 | RESISTOR, American symbol
 | 12 | AD7685BRMZRL7CT-ND |  | AD7685RM-10 | AD7685RM-10 | MSOP-10 | 4 | ADC1, ADC2, ADC3, ADC4
 | 6 | AD8616ARZ-REEL7CT-ND |  | AD8616R-8 | AD8616R-8 | SOIC8 | 2 | OPAMP1, OPAMP2
 | 3 | ADR435BRZ-REEL7CT-ND |  | ADR435RM-8 | ADR435RM-8 | SOIC8 | 1 | REF1
 | 3 | CKN9104CT-ND | Robin | COM08720 | COM08720 | COM08720 | 1 | SW1
 | 3 |  | Andrew | Debug Header | 1.27MM_HDR_2X5 | 1.27MM_2X5 | 1 | J22
 | 3 | 490-1046-1-ND | Robert | FB0805/600R/200mA(201209-601) | L-US0805-C-NOSILK | 0805-C-NOSILK | 1 | L3 | INDUCTOR, American symbol
 | 3 | 576-4177-1-ND |  | KSZ8081 | KSZ8081 | QFN-24 | 1 | U3
 | 3 | LMZ14202HTZ/NOPBCT-ND |  | LMZ14202HTZ | LMZ14202HTZ | PFM-7 | 1 | VR2
 | 3 | 670-1190-1-ND | Robin | MINI-USB-32005-301 | MINI-USB-32005-301 | 32005-301 | 1 | X4 | MINI USB-B Conector |  |  | unknown | unknown
 | 3 |  | Not populated | NU | C-EUC0402 | C0402 | 1 | C92 | CAPACITOR, European symbol
 | 3 | SMAJ58ALFTR-ND |  | SMAJ58A | SUPPRESSOR-SMBJ | SMBJ | 1 | D4 | Suppressor diode
 | 3 | 497-11605-ND |  | STM32F407ZXT | STM32F407ZXT | LQFP-100 | 1 | U1
 | 3 | 296-28078-1-ND |  | TL751M08QKVURQ1 | TL751M08QKVURQ1 | PG-TO252-5-11 | 1 | VR3 | 8V power supply.
 | 3 | TLE42754DINCT-ND |  | TLE4275-QKVU | TLE4275-QKVU | PG-TO252-5-11 | 1 | VR8
 | 3 | 296-20658-1-ND |  | TLV1117-33IKVU | TLV1117-33IKVU | PG-TO252-3-11 | 1 | VR6
 | 3 | MAX5984AETI+-ND | Robert | MAX5984A | MAX5984 | TQFN-28 | 1 | IC2 |  |  |  |  |  |  | C
NON-DIGIKEY ITEMS
 | 1 | CHB75W-24S48 | http://www.psui.com/ | CHB75W-24S48 | CHB75W | CHB75W | 1 | POE
